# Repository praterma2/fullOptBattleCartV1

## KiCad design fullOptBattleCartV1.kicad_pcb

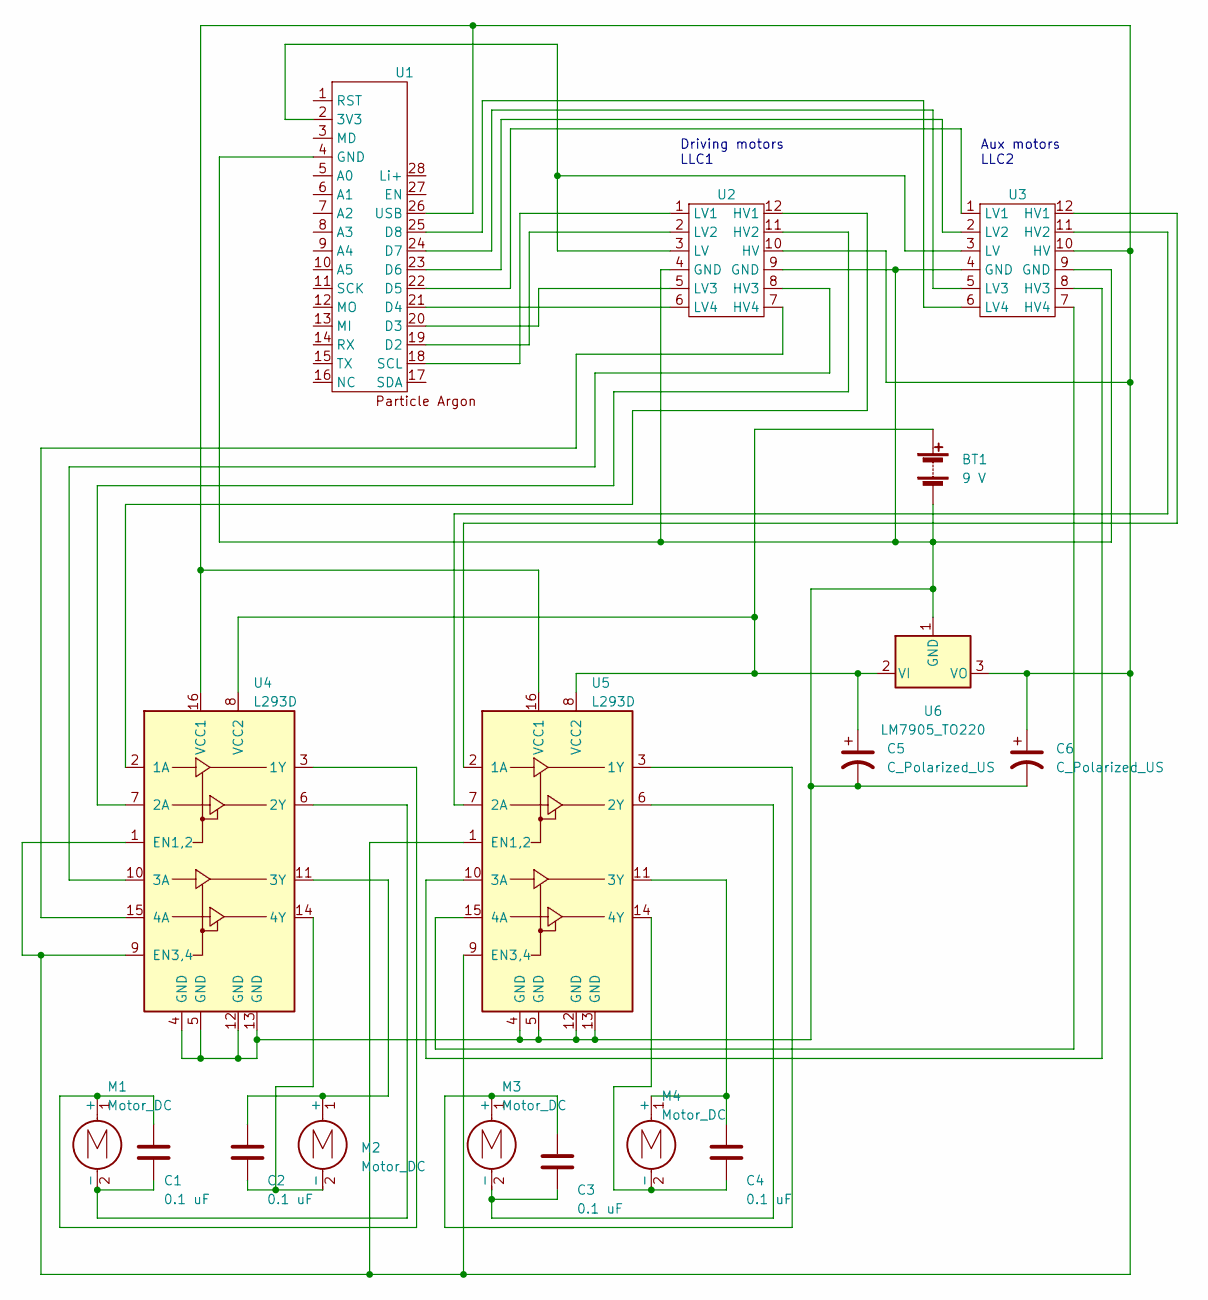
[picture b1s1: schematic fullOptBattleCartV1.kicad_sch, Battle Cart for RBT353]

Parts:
BT1: 9 V; JST_XH_B2B-XH-A_1x02_P2.50mm_Vertical
C1, C2, C3, C4: 0.1 uF; C_Disc_D5.0mm_W2.5mm_P2.50mm
C5, C6: C_Polarized_US; CP_Radial_D10.0mm_P2.50mm
M1, M2, M3, M4: Motor_DC; JST_XH_B2B-XH-AM_1x02_P2.50mm_Vertical
U1: Argon
U2, U3: LLC
U4, U5: L293D; DIP-16_W7.62mm
U6: LM7905_TO220; TO-220-3_Vertical

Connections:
unnamed: BT1.1 (+), C5.1, U4.8 (VCC2), U5.8 (VCC2), U6.2 (VI)
unnamed: BT1.2 (-), C5.2, C6.2, U1.4 (GND), U2.4 (GND), U2.9 (GND), U3.4 (GND), U3.9 (GND), U4.4 (GND), U4.5 (GND), U4.12 (GND), U4.13 (GND), U5.4 (GND), U5.5 (GND), U5.12 (GND), U5.13 (GND), U6.1 (GND)
unnamed: C1.1, M1.1 (+), U4.3 (1Y)
unnamed: C1.2, M1.2 (-), U4.6 (2Y)
unnamed: C2.1, M2.1 (+), U4.11 (3Y)
unnamed: C2.2, M2.2 (-), U4.14 (4Y)
unnamed: C3.1, M3.1 (+), U5.3 (1Y)
unnamed: C3.2, M3.2 (-), U5.6 (2Y)
unnamed: C4.1, M4.1 (+), U5.11 (3Y)
unnamed: C4.2, M4.2 (-), U5.14 (4Y)
unnamed: U1.2 (3V3), U2.3 (LV), U3.3 (LV)
unnamed: U1.19 (D2), U2.2 (LV2)
unnamed: U1.20 (D3), U2.5 (LV3)
unnamed: U1.21 (D4), U2.6 (LV4)
unnamed: U1.22 (D5), U3.1 (LV1)
unnamed: U1.23 (D6), U3.2 (LV2)
unnamed: U1.24 (D7), U3.5 (LV3)
unnamed: U1.25 (D8), U3.6 (LV4)
unnamed: U1.18 (SCL), U2.1 (LV1)
unnamed: C6.1, U1.26 (USB), U2.10 (HV), U3.10 (HV), U4.1 (EN1,2), U4.9 (EN3,4), U4.16 (VCC1), U5.1 (EN1,2), U5.9 (EN3,4), U5.16 (VCC1), U6.3 (VO)
unnamed: U2.12 (HV1), U4.2 (1A)
unnamed: U2.11 (HV2), U4.7 (2A)
unnamed: U2.8 (HV3), U4.10 (3A)
unnamed: U2.7 (HV4), U4.15 (4A)
unnamed: U3.12 (HV1), U5.2 (1A)
unnamed: U3.11 (HV2), U5.7 (2A)
unnamed: U3.8 (HV3), U5.10 (3A)
unnamed: U3.7 (HV4), U5.15 (4A)

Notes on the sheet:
Driving motors LLC1
Aux motors LLC2

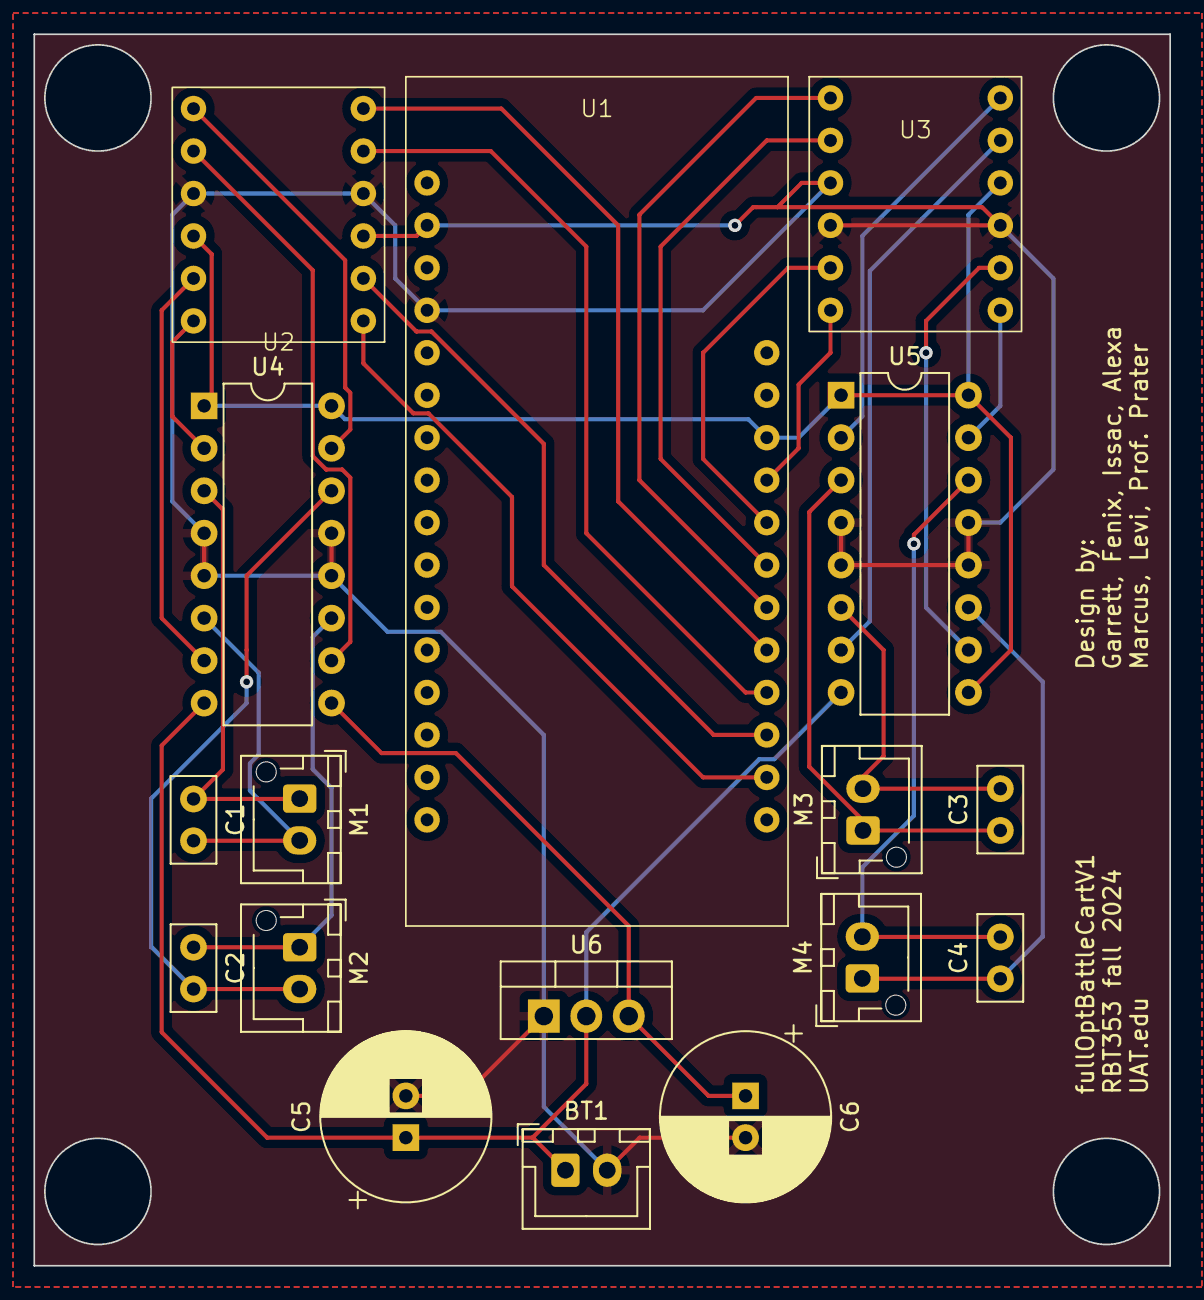
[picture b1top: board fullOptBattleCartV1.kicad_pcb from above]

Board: 2 copper layers, 67.9 x 73.7 mm, 17 parts (0 on the bottom side), 28 nets.

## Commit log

2024-11-13 battlecart modification
